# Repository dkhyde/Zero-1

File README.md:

# Zero-1
Replacement Keyboard for Hornby Zero 1 Master Unit

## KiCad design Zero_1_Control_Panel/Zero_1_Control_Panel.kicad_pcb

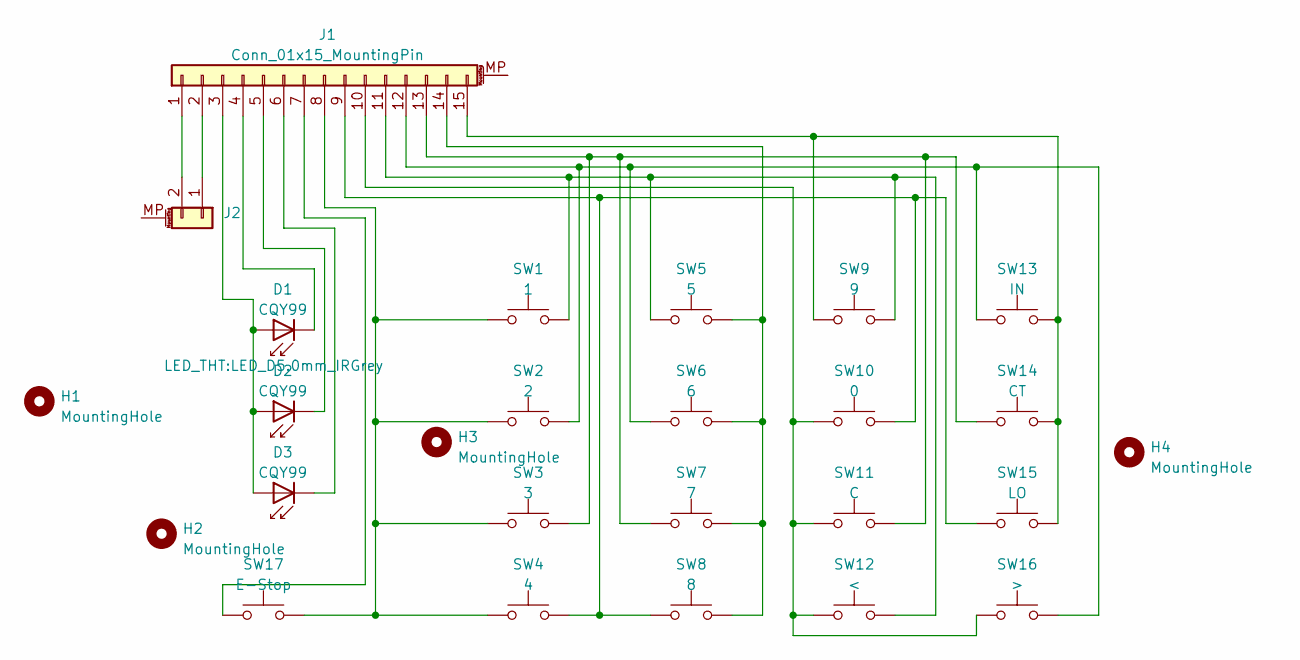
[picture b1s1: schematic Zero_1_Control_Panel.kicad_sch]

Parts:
D1, D2, D3: CQY99; LED_D5.0mm_IRGrey
H1, H2, H3, H4: MountingHole; MountingHole_3.2mm_M3
J1: Conn_01x15_MountingPin; PinHeader_1x15_P2.54mm_Vertical
J2: Conn_01x02_MountingPin; PinHeader_1x02_P2.54mm_Vertical
SW1: 1; SW_PUSH_6mm_H5mm_single
SW2: 2; SW_PUSH_6mm_H5mm_single
SW3: 3; SW_PUSH_6mm_H5mm_single
SW4: 4; SW_PUSH_6mm_H5mm_single
SW5: 5; SW_PUSH_6mm_H5mm_single
SW6: 6; SW_PUSH_6mm_H5mm_single
SW7: 7; SW_PUSH_6mm_H5mm_single
SW8: 8; SW_PUSH_6mm_H5mm_single
SW9: 9; SW_PUSH_6mm_H5mm_single
SW10: 0; SW_PUSH_6mm_H5mm_single
SW11: C; SW_PUSH_6mm_H5mm_single
SW12: <; SW_PUSH_6mm_H5mm_single
SW13: IN; SW_PUSH_6mm_H5mm_single
SW14: CT; SW_PUSH_6mm_H5mm_single
SW15: LO; SW_PUSH_6mm_H5mm_single
SW16: >; SW_PUSH_6mm_H5mm_single
SW17: E-Stop; SW_PUSH_6mm_H5mm_single

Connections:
unnamed: D1.2 (A), D2.2 (A), D3.2 (A), J1.3
unnamed: D1.1 (K), J1.4
unnamed: D2.1 (K), J1.5
unnamed: D3.1 (K), J1.6
unnamed: J1.1, J2.2
unnamed: J1.2, J2.1
unnamed: J1.7, SW17.1
unnamed: J1.8, SW1.1, SW2.1, SW3.1, SW4.1, SW17.2
unnamed: J1.9, SW4.2, SW8.1, SW10.2, SW15.1
unnamed: J1.10, SW10.1, SW11.1, SW12.1, SW16.1
unnamed: J1.11, SW1.2, SW5.1, SW9.2, SW12.2
unnamed: J1.12, SW2.2, SW6.1, SW13.1, SW16.2
unnamed: J1.13, SW3.2, SW7.1, SW11.2, SW14.1
unnamed: J1.14, SW5.2, SW6.2, SW7.2, SW8.2
unnamed: J1.15, SW9.1, SW13.2, SW14.2, SW15.2

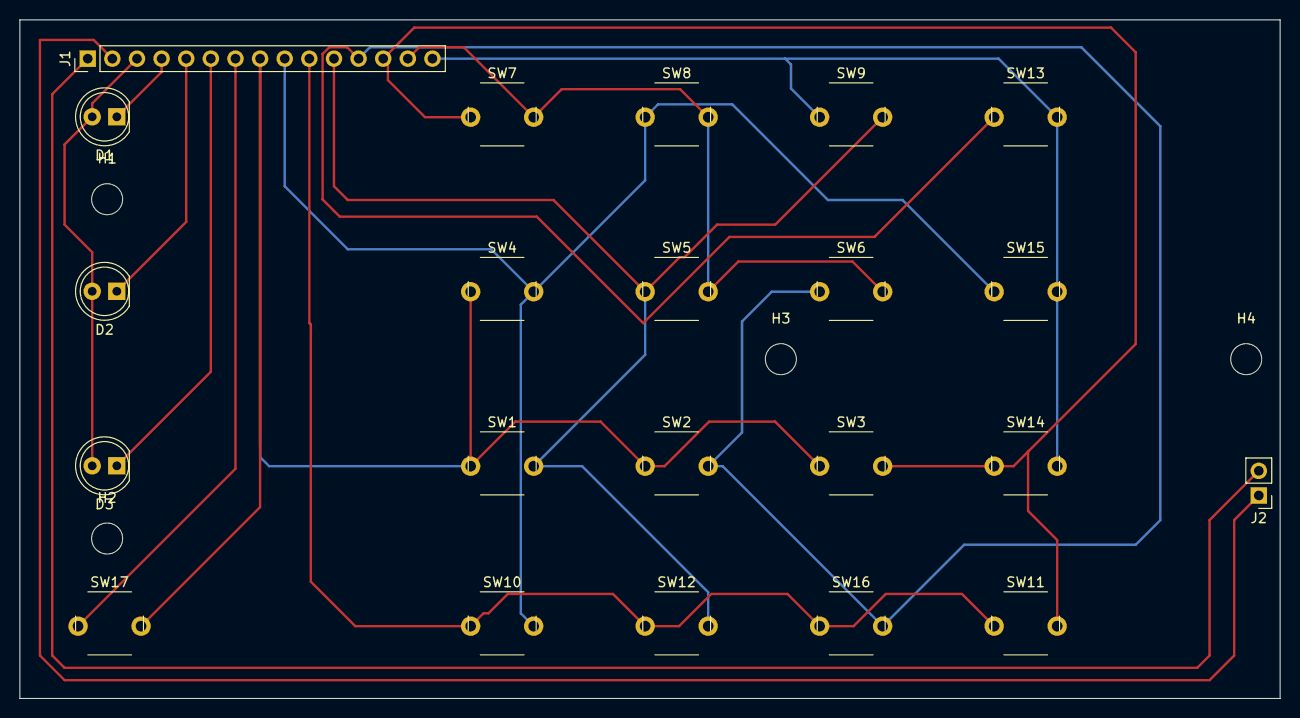
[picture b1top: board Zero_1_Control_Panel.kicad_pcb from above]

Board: 2 copper layers, 130.0 x 70.0 mm, 26 parts (0 on the bottom side), 15 nets.

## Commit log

2024-10-28 First draft
2024-11-06 3d Print Buttons
2024-11-06 Re-org
